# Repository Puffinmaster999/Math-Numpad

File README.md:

# Math Numpad
This is a [**Hack Club**](https://hackclub.com) project!

This is a math-focused numpad designed in [Ergogen](https://ergogen.xyz/) and [KiCad](https://www.kicad.org/)

---

## Why I Made This
I first saw this amazing [YouTube video](https://youtu.be/7UXsD7nSfDY) where Christian Selig made a custom keyboard that suited his liking perfectly! However, the keyboard that I am using is so good for my personal liking that I didn't want to change my entire keyboard. Rather as a student still doing math, I thought that it would be nice to have a numpad that would be custom made for me! 

The layout of the numpad was inspired by the **Casio FX-300ES PLUS 2nd Edition calculator**. It has a lot of the necessary math functions and I was able to use this as my base to add my personal functions on top of. If you look at the overall layout of the keyboard it will be similar to the math functions that exist on this calculator! However, the most important thing for me was the ability for the numpad to be able to do some math! This way if I want to use this as a calculator, I can! the only issue that I see is that this might not be allowed for online tests, for personal use however I think this is a perfect tool!

## Screenshots & Layout Plan

## Tech Stack & How It Was Made
- Layout: Ergogen
- PCB Design: KiCAD
- Firmware: ZMK (**WIP**)

Following the YouTube video I first got used to how Ergogen worked and designed a rough outline. Although that rough outline wasn't the worst, looking back I feel like I could have thought out my design better. That file is located [here](math_numpad.dxf). I brought that into KiCAD and that's where most of the thinking began. Here I decided to do some real design choices and figured out how I really wanted the keyboard to feel like. I even used some paper to see if I would like the feel. After all of that is done I needed to make sure that the work that I did is reproducible and someone else can use! This is this GitHub project! Hope you enjoy!~

## BOM (Bill of Materials)
|Part|Quantity|Link/Notes|
|---|---|---|
|Microcontroller|1|[nice!nano](https://typeractive.xyz/products/nice-nano)|
|Rotary Encoder (Knob)|2|[Bourns PEC11R](https://www.digikey.com/en/products/detail/bourns-inc/PEC11R-4220F-S0024/4499660)|
|MX Switches|27|Any MX-style switches you prefer!|
|Keycaps|27|MX compatible keycaps! (2 2u size switches)|
|Diodes|27|Any standard 2-pin SOD-123 package diode|

## Repo Files & How to Build It
- KiCAD Project: math_numpad.kicad_pcb, math_numpad.kicad_prl, math_numpad.kicad_pro
- Gerbers: production/math_numpad_gerbers.zip

1. Download [production/math_numpad_gerbers.zip](production/math_numpad_gerbers.zip) and upload it to a PCB manufacturer (like JLCPCB or PCBWay).
2. Solder the diodes, switches, rotary encoders, and nice!nano onto the PCB
3. **WIP** flash the firmware

## AI disclosure
A very small amount of ai was used during the research phase! No ai was used during the PCB, and shipping process of this project!

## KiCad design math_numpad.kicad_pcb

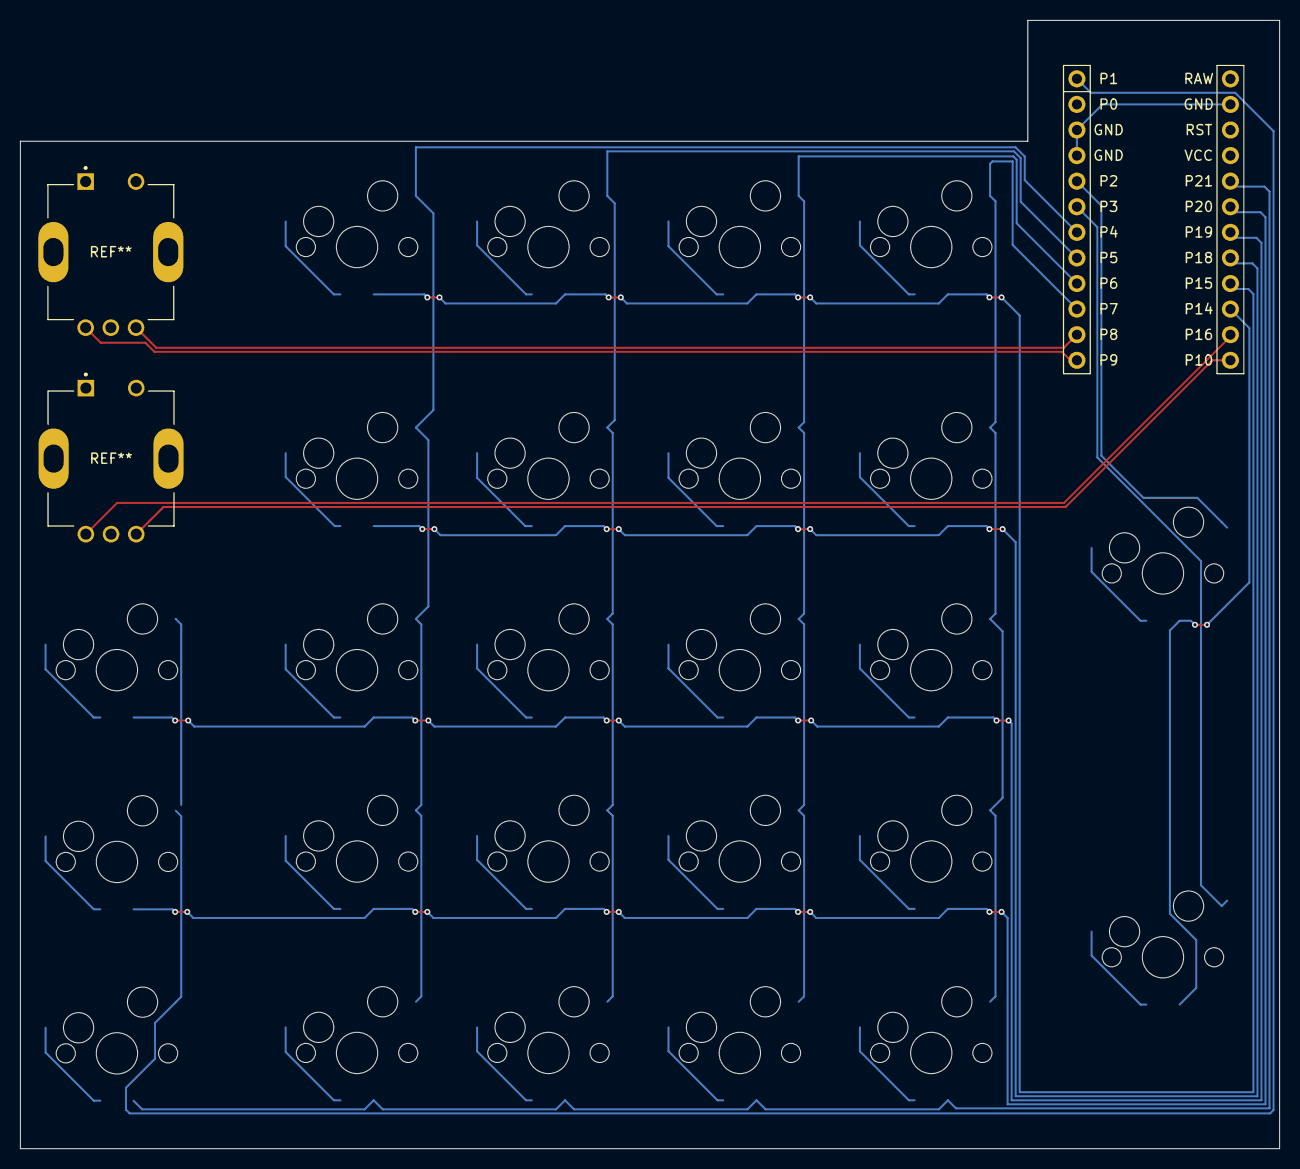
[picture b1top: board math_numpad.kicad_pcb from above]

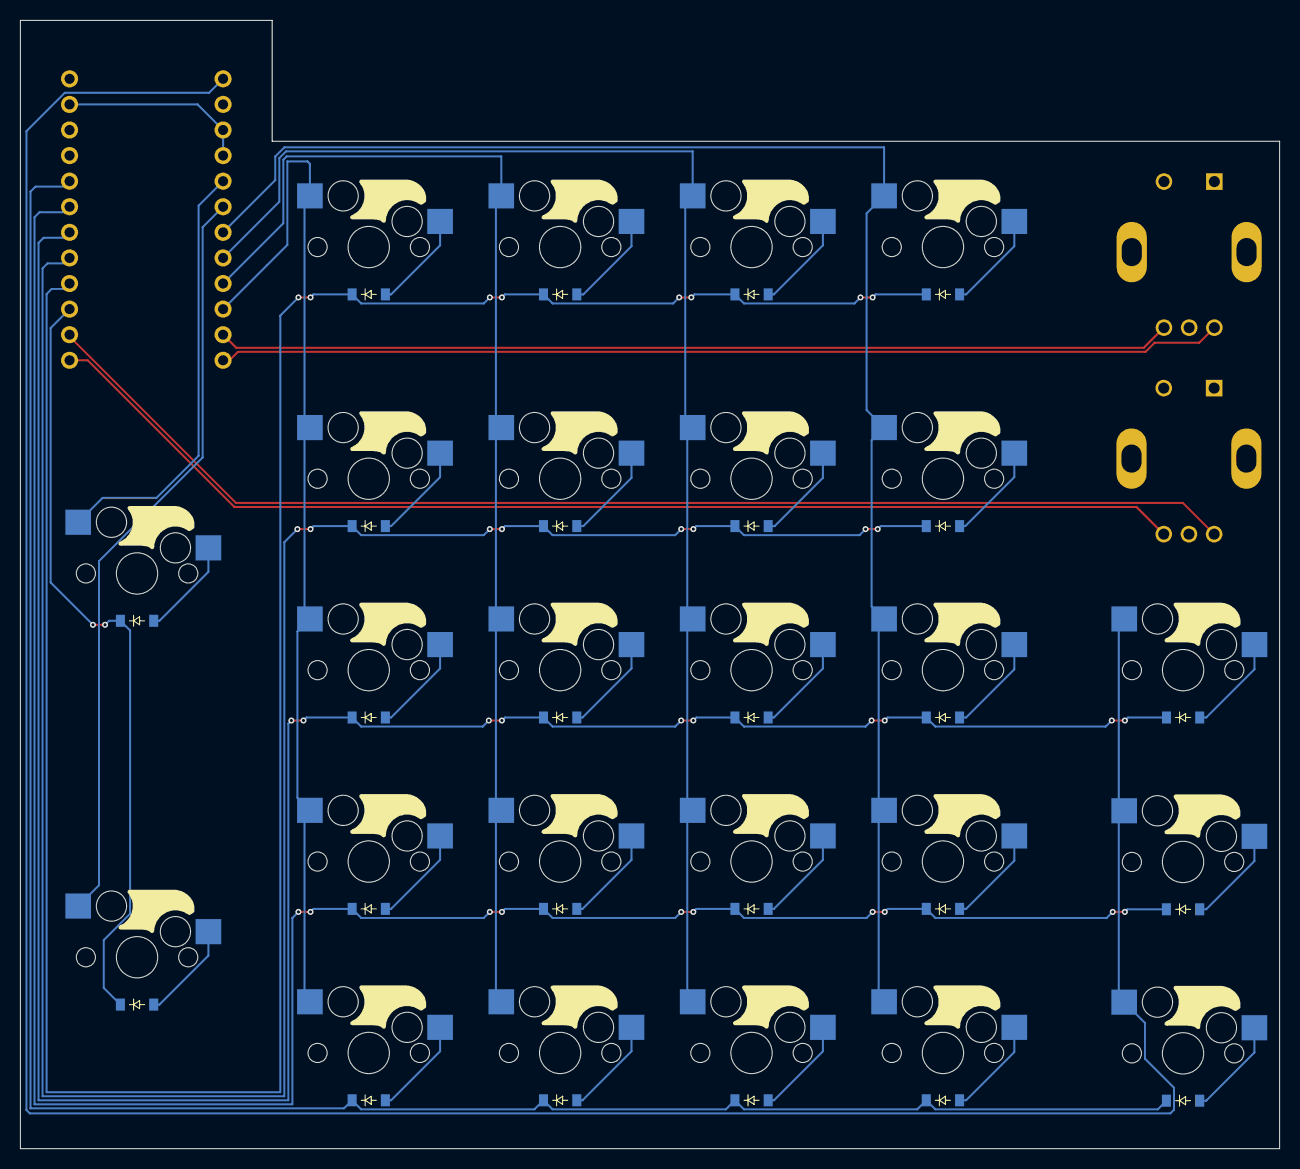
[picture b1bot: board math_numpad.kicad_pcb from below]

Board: 2 copper layers, 125.0 x 112.0 mm, 51 parts (50 on the bottom side), 39 nets.

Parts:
D1, D2, D2#2, D3, D3#2, D3#3, D4, D5, D6, D7, D8, D9, D10, D11, D12, D13, D14, D15, D16, D17, D18, D19, D20, D21, D22: diode_tht_sod123
MCU1: mcu_nice_nano
S1, S2, S2#2, S3, S3#2, S3#3, S4, S5, S6, S7, S8, S9, S10, S11, S12, S13, S14, S15, S16, S17, S18, S19, S20, S21, S22: switch_mx

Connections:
GND: MCU1.2, MCU1.21, MCU1.22
P1: MCU1.24, S2#2.2, S3.2, S3#3.2
P2: MCU1.20, S18.2
P3: MCU1.19, S17.2
P4: MCU1.18, S1.2, S2.2, S3#2.2, S4.2, S19.2
P5: MCU1.17, S5.2, S6.2, S7.2, S8.2, S20.2
P6: MCU1.16, S9.2, S10.2, S11.2, S12.2, S21.2
P7: MCU1.15, S13.2, S14.2, S15.2, S16.2, S22.2
P14: D17.1, D18.1, MCU1.10
P15: D19.1, D20.1, D21.1, D22.1, MCU1.9
P18: D4.1, D8.1, D12.1, D16.1, MCU1.8
P19: D3.1, D3#3.1, D7.1, D11.1, D15.1, MCU1.7
P20: D2.1, D3#2.1, D6.1, D10.1, D14.1, MCU1.6
P21: D1.1, D2#2.1, D5.1, D9.1, D13.1, MCU1.5
function_1: D2#2.2, S2#2.1
function_2: D3#2.2, S3.1
function_3: D3.2, S3#3.1
matrix_1_1: D1.2, S1.1
matrix_1_2: D2.2, S2.1
matrix_1_3: D3#3.2, S3#2.1
matrix_1_4: D4.2, S4.1
matrix_2_1: D5.2, S5.1
matrix_2_2: D6.2, S6.1
matrix_2_3: D7.2, S7.1
matrix_2_4: D8.2, S8.1
matrix_3_1: D9.2, S9.1
matrix_3_2: D10.2, S10.1
matrix_3_3: D11.2, S11.1
matrix_3_4: D12.2, S12.1
matrix_4_1: D13.2, S13.1
matrix_4_2: D14.2, S14.1
matrix_4_3: D15.2, S15.1
matrix_4_4: D16.2, S16.1
side_column_1_1: D17.2, S17.1
side_column_1_2: D18.2, S18.1
top_row_1_1: D19.2, S19.1
top_row_2_1: D20.2, S20.1
top_row_3_1: D21.2, S21.1
top_row_4_1: D22.2, S22.1

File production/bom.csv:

Designator,Footprint,Quantity,Value,LCSC Part #
"D1, D10, D11, D12, D13, D14, D15, D16, D17, D18, D19, D2_2, D2, D20, D21, D22, D3_3, D3_2, D3, D4, D5, D6, D7, D8, D9",diode_tht_sod123,25,,
"S1, S10, S11, S12, S13, S14, S15, S16, S17, S18, S19, S2_2, S2, S20, S21, S22, S3_3, S3_2, S3, S4, S5, S6, S7, S8, S9",switch_mx,25,,
